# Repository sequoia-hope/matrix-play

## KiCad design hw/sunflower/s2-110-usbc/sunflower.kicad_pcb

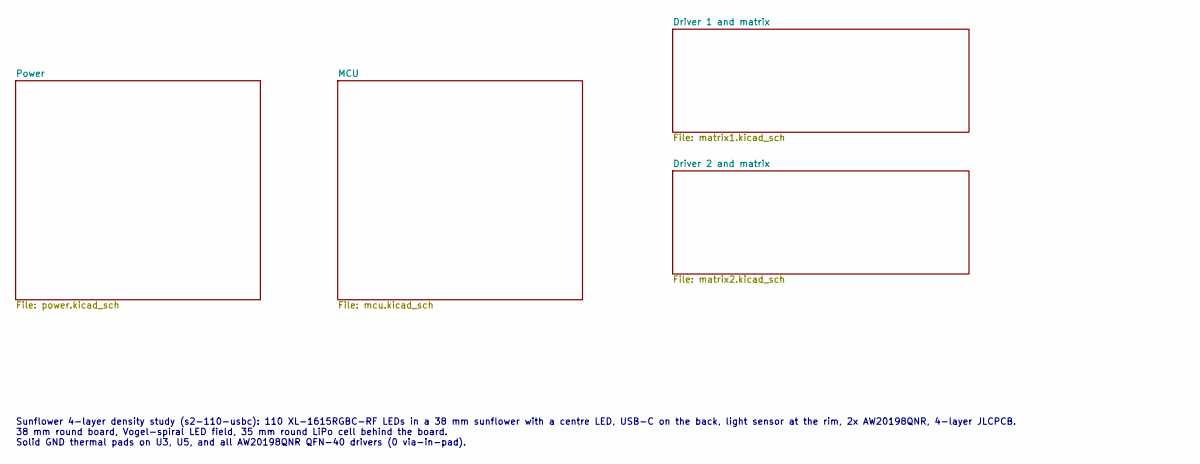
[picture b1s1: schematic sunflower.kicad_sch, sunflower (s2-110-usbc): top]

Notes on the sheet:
Sunflower 4-layer density study (s2-110-usbc): 110 XL-1615RGBC-RF LEDs in a 38 mm sunflower with a centre LED, USB-C on the back, light sensor at the rim, 2x AW20198QNR, 4-layer JLCPCB. 38 mm round board, Vogel-spiral LED field, 35 mm round LiPo cell behind the board. Solid GND thermal pads on U3, 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

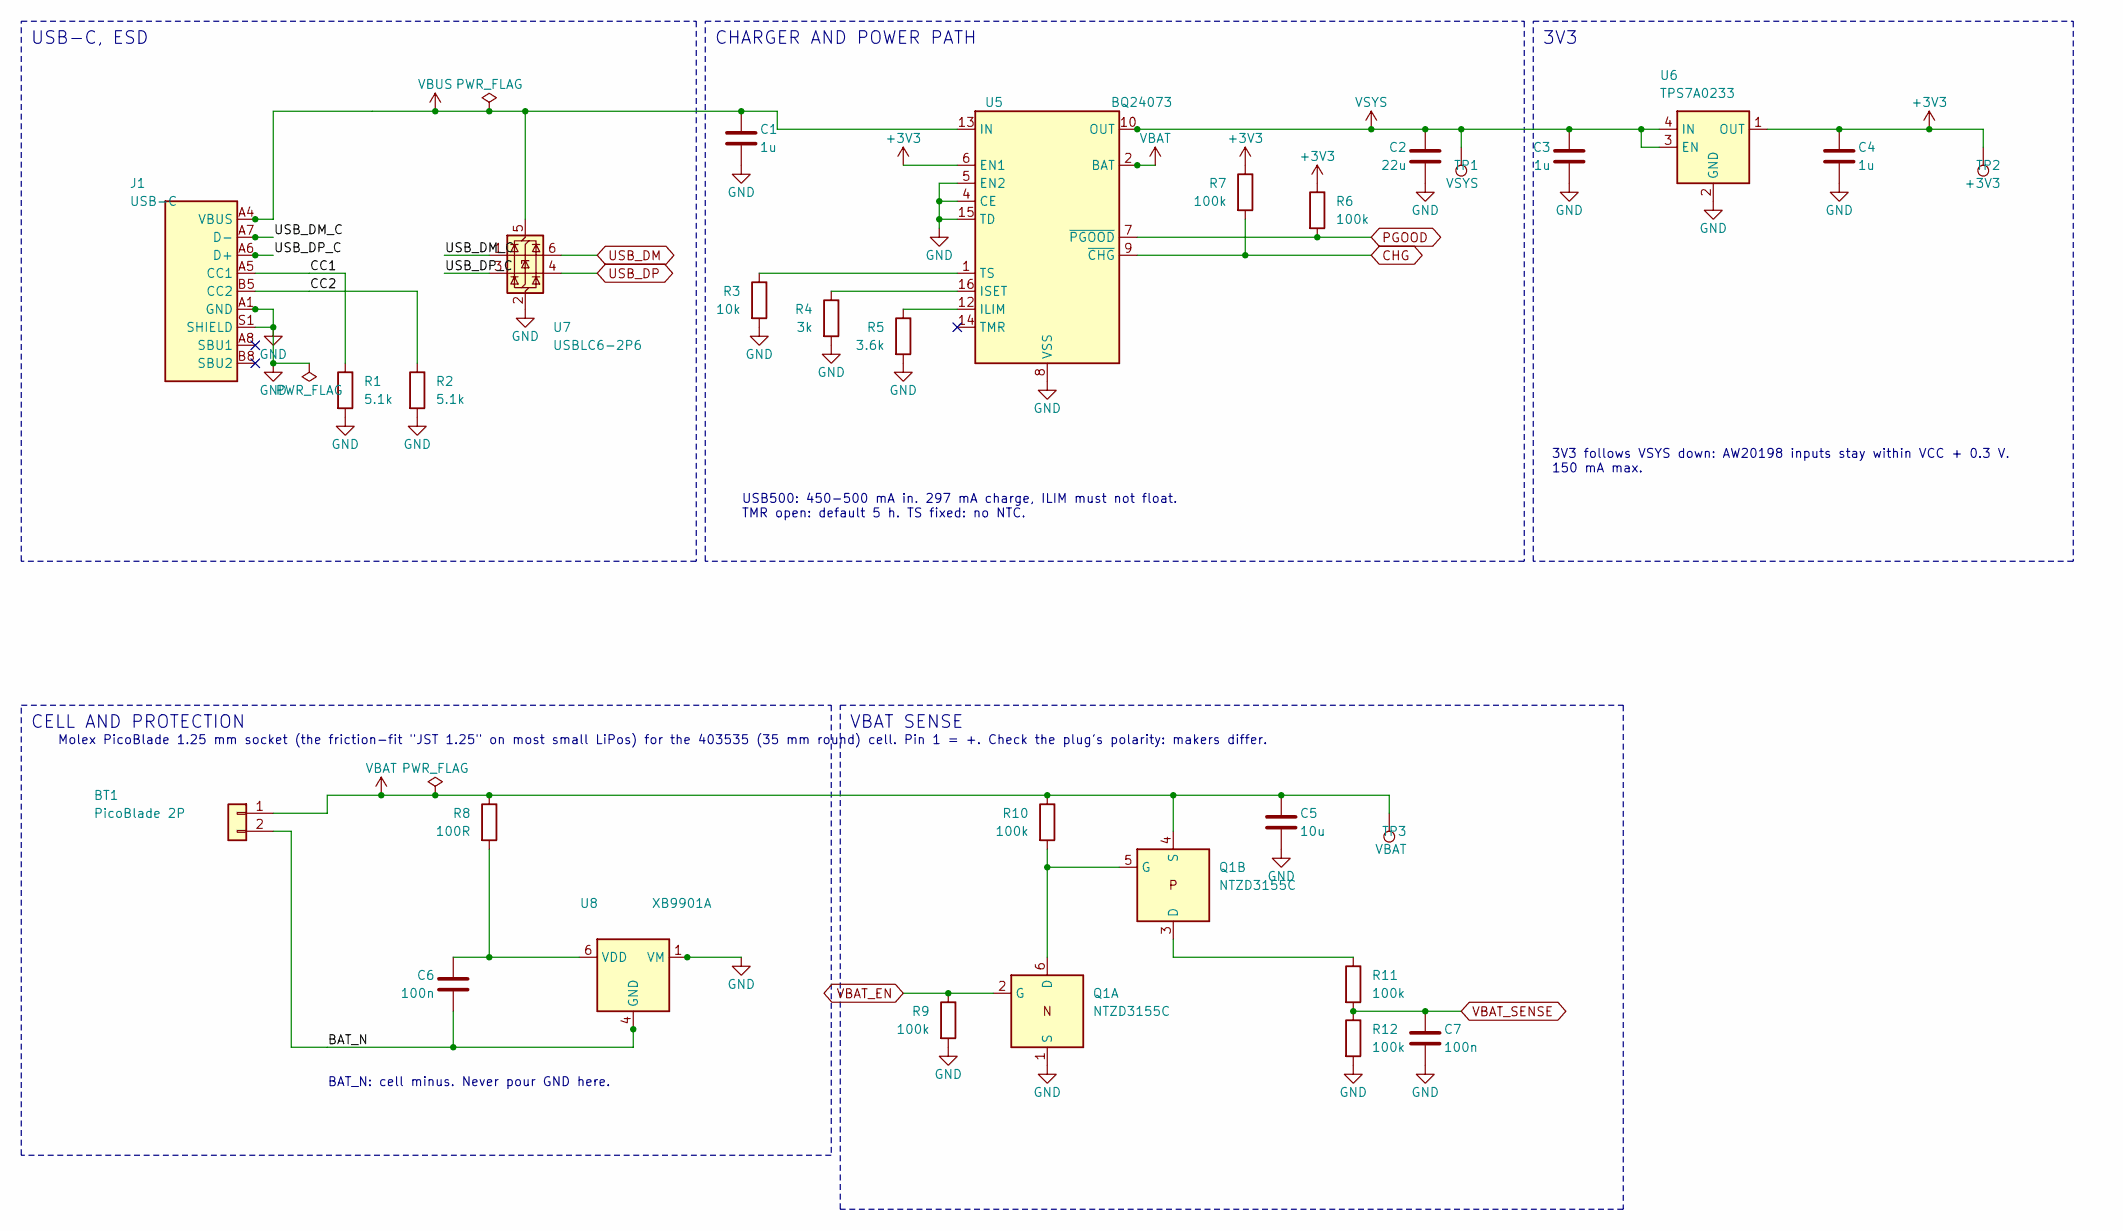
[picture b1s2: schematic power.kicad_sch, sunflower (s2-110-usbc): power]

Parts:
BT1: PicoBlade 2P; Molex_PicoBlade_53261-0271_1x02-1MP_P1.25mm_Horizontal; MPN 53261-0271; LCSC C177225
C1, C3, C4: 1u; C_0402_1005Metric; MPN CL05A105KA5NQNC; LCSC C52923
C2: 22u; C_0603_1608Metric; MPN CL10A226MP8NUNE; LCSC C86295
C5: 10u; C_0603_1608Metric; MPN CL10A106KP8NNNC; LCSC C19702
C6, C7: 100n; C_0402_1005Metric; MPN CL05B104KO5NNNC; LCSC C1525
J1: USB-C; USB_C_Receptacle_HRO_TYPE-C-31-M-12; MPN TYPE-C-31-M-12; LCSC C165948
Q1: NTZD3155C; SOT-563; MPN NTZD3155CT1G; LCSC C236117
R1, R2: 5.1k; R_0402_1005Metric; MPN 0402WGF5101TCE; LCSC C25905
R3: 10k; R_0402_1005Metric; MPN 0402WGF1002TCE; LCSC C25744
R4: 3k; R_0402_1005Metric; MPN 0402WGF3001TCE; LCSC C25784
R5: 3.6k; R_0402_1005Metric; MPN 0402WGF3601TCE; LCSC C25891
R6, R7, R9, R10, R11, R12: 100k; R_0402_1005Metric; MPN 0402WGF1003TCE; LCSC C25741
R8: 100R; R_0402_1005Metric; MPN 0402WGF1000TCE; LCSC C25076
TP1: VSYS; TestPoint_Pad_D1.0mm_CrtYd0.75
TP2: +3V3; TestPoint_Pad_D1.0mm_CrtYd0.75
TP3: VBAT; TestPoint_Pad_D1.0mm_CrtYd0.75
U5: BQ24073; QFN-16-1EP_3x3mm_P0.5mm_EP1.7x1.7mm; MPN BQ24073RGTR; LCSC C15220
U6: TPS7A0233; Texas_X2SON-4_1x1mm_P0.65mm; MPN TPS7A0233PDQNR; LCSC C2860046
U7: USBLC6-2P6; SOT-666; MPN USBLC6-2P6; LCSC C15999
U8: XB9901A; XySemi_DFN-6_1.8x1.4mm; MPN XB9901A; LCSC C669687

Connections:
+3V3: C4.1, R6.1, R7.1, TP2.1, U5.6 (EN1), U6.1 (OUT); also elsewhere on the board
/Power/BAT_N: BT1.2, C6.2, U8.4 (GND), U8.5 (GND)
/Power/CC1: J1.A5 (CC1), R1.1
/Power/CC2: J1.B5 (CC2), R2.1
/Power/USB_DM_C: J1.A7 (D-), J1.B7 (D-), U7.1 (I/O1)
/Power/USB_DP_C: J1.A6 (D+), J1.B6 (D+), U7.3 (I/O2)
CHG: R7.2, U5.9 (~CHG); also elsewhere on the board
unnamed: Q1.5 (G), Q1.6 (D), R10.2
unnamed: Q1.3 (D), R11.1
unnamed: R5.1, U5.12 (ILIM)
unnamed: R4.1, U5.16 (ISET)
unnamed: R3.1, U5.1 (TS)
unnamed: C6.1, R8.2, U8.6 (VDD)
PGOOD: R6.2, U5.7 (~PGOOD); also elsewhere on the board
USB_DM: U7.6 (I/O1); also elsewhere on the board
USB_DP: U7.4 (I/O2); also elsewhere on the board
VBAT_EN: Q1.2 (G), R9.1; also elsewhere on the board
VBAT_SENSE: C7.1, R11.2, R12.1; also elsewhere on the board
VSYS: C2.1, C3.1, TP1.1, U5.10 (OUT), U5.11 (OUT), U6.3 (EN), U6.4 (IN); also elsewhere on the board

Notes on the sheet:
USB-C, ESD
USB500: 450-500 mA in. 297 mA charge, ILIM must not float. TMR open: default 5 h. TS fixed: no NTC.
CHARGER AND POWER PATH
3V3 follows VSYS down: AW20198 inputs stay within VCC + 0.3 V. 150 mA max.
3V3
Molex PicoBlade 1.25 mm socket (the friction-fit "JST 1.25" on most small LiPos) for the 403535 (35 mm round) cell. Pin 1 = +. Check the plug's polarity: makers differ.
BAT_N: cell minus. Never pour GND here.
CELL AND PROTECTION
VBAT SENSE

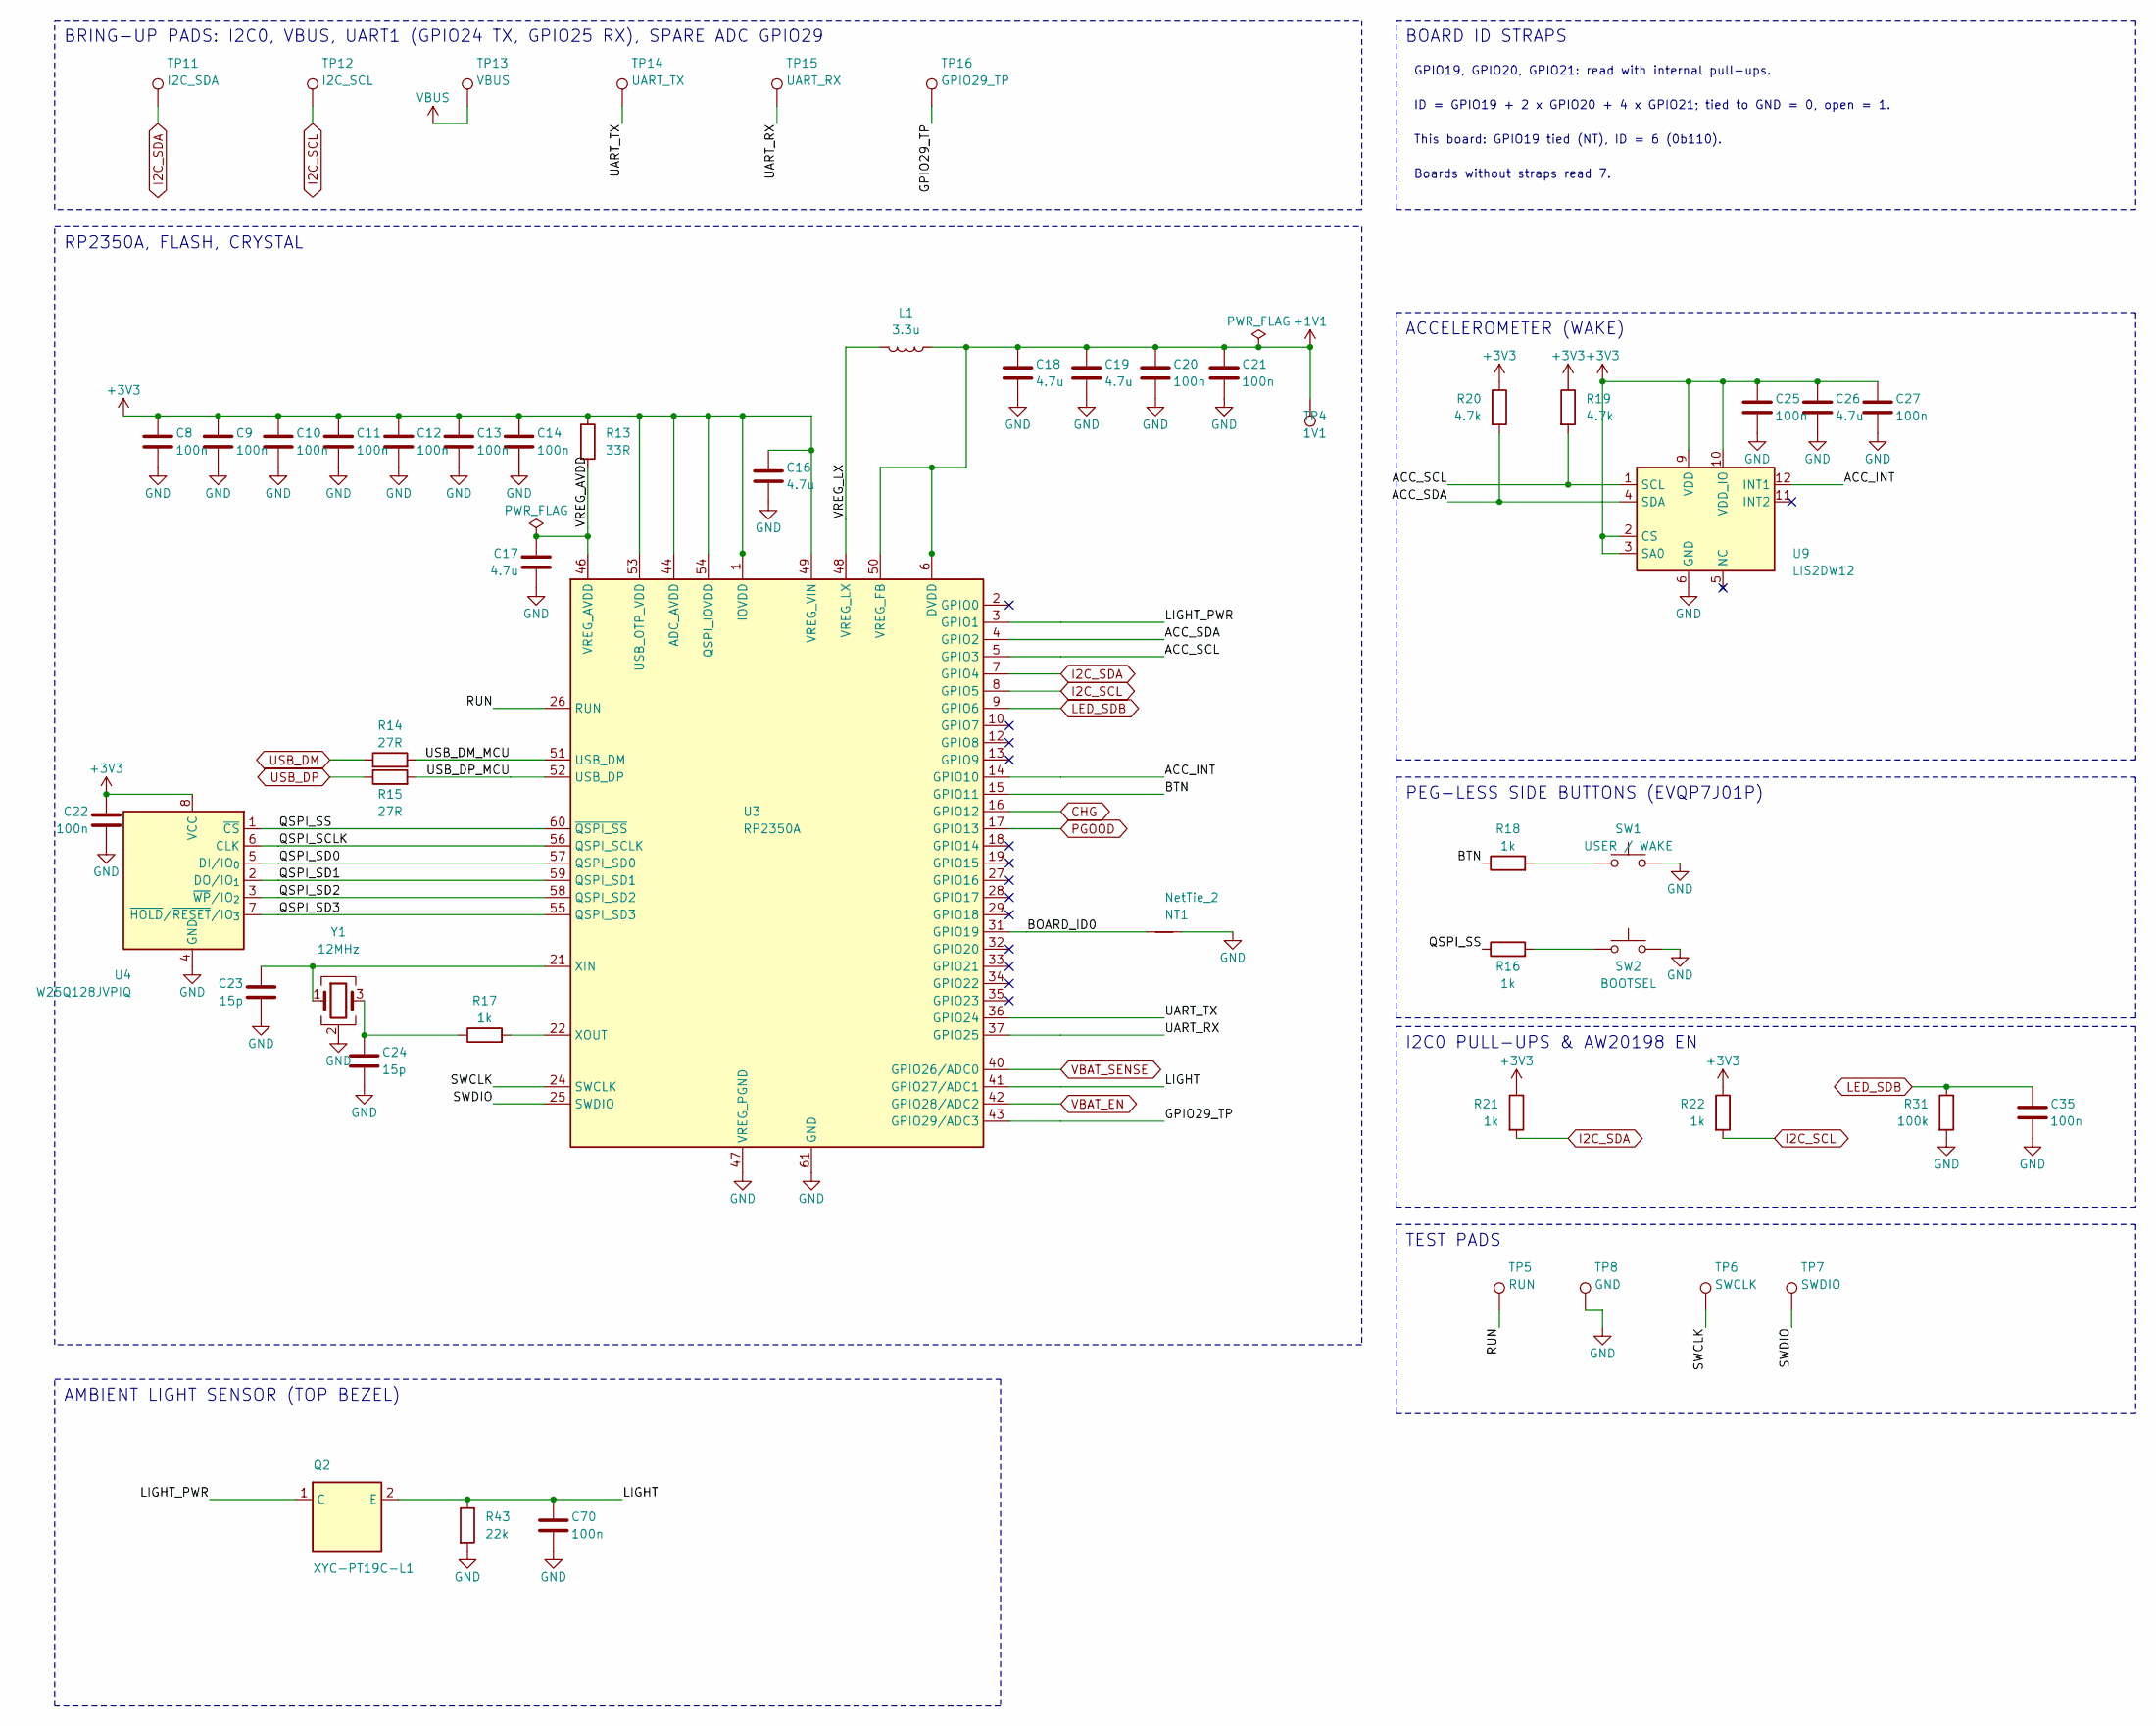
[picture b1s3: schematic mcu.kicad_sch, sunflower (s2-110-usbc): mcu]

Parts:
C8, C9, C10, C11, C12, C13, C14, C20, C21, C22, C25, C27, C35, C70: 100n; C_0402_1005Metric; MPN CL05B104KO5NNNC; LCSC C1525
C16, C18: 4.7u; C_0402_1005Metric_small_pads; MPN CL05A475MP5NRNC; LCSC C23733
C17, C19, C26: 4.7u; C_0402_1005Metric; MPN CL05A475MP5NRNC; LCSC C23733
C23, C24: 15p; C_0402_1005Metric; MPN 0402CG150J500NT; LCSC C1548
L1: 3.3u; L_pol_2016; MPN AOTA-B201610S3R3-101-T; LCSC C42411119
NT1: NetTie_2; NetTie-2_SMD_Pad0.5mm
Q2: XYC-PT19C-L1; SENSOR_ALS-PT19; MPN XYC-PT19C-L1; LCSC C2693594
R13: 33R; R_0402_1005Metric; MPN 0402WGF330JTCE; LCSC C25105
R14, R15: 27R; R_0402_1005Metric; MPN 0402WGF270JTCE; LCSC C25100
R16, R17, R18, R21, R22: 1k; R_0402_1005Metric; MPN 0402WGF1001TCE; LCSC C11702
R19, R20: 4.7k; R_0402_1005Metric; MPN 0402WGF4701TCE; LCSC C25900
R31: 100k; R_0402_1005Metric; MPN 0402WGF1003TCE; LCSC C25741
R43: 22k; R_0402_1005Metric; MPN 0402WGF2202TCE; LCSC C25768
SW1: USER / WAKE; SW_Panasonic_EVQP7J; MPN EVQP7J01P; LCSC C2828254
SW2: BOOTSEL; SW_Panasonic_EVQP7J; MPN EVQP7J01P; LCSC C2828254
TP4: 1V1; TestPoint_Pad_D1.0mm_CrtYd0.75
TP5: RUN; TestPoint_Pad_D1.0mm_CrtYd0.75
TP6: SWCLK; TestPoint_Pad_D1.0mm_CrtYd0.75
TP7: SWDIO; TestPoint_Pad_D1.0mm_CrtYd0.75
TP8: GND; TestPoint_Pad_D1.0mm_CrtYd0.75
TP11: I2C_SDA; TestPoint_Pad_D1.0mm_CrtYd0.75
TP12: I2C_SCL; TestPoint_Pad_D1.0mm_CrtYd0.75
TP13: VBUS; TestPoint_Pad_D1.0mm_CrtYd0.75
TP14: UART_TX; TestPoint_Pad_D1.0mm_CrtYd0.75
TP15: UART_RX; TestPoint_Pad_D1.0mm_CrtYd0.75
TP16: GPIO29_TP; TestPoint_Pad_D1.0mm_CrtYd0.75
U3: RP2350A; RP2350-QFN-60-1EP_7x7_P0.4mm_EP3.4x3.4mm_ThermalVias; MPN RP2350A; LCSC C42411118
U4: W25Q128JVPIQ; WSON-8_6x5mm_P1.27mm_NoEPCopper; MPN W25Q128JVPIQ; LCSC C190862
U9: LIS2DW12; LGA-12_2x2mm_P0.5mm; MPN LIS2DW12TR; LCSC C189624
Y1: 12MHz; Crystal_SMD_3225-4Pin_3.2x2.5mm; MPN ABM8-272-T3; LCSC C20625731

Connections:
+3V3: C8.1, C9.1, C10.1, C11.1, C12.1, C13.1, C14.1, C16.1, C22.1, C25.1, C26.1, C27.1, R13.1, R19.1, R20.1, R21.1, R22.1, U3.1 (IOVDD), U3.11 (IOVDD), U3.20 (IOVDD), U3.30 (IOVDD), U3.38 (IOVDD), U3.44 (ADC_AVDD), U3.45 (IOVDD), U3.49 (VREG_VIN), U3.53 (USB_OTP_VDD), U3.54 (QSPI_IOVDD), U4.8 (VCC), U9.2 (CS), U9.3 (SA0), U9.9 (VDD), U9.10 (VDD_IO); also elsewhere on the board
/MCU/ACC_INT: U3.14 (GPIO10), U9.12 (INT1)
/MCU/ACC_SCL: R19.2, U3.5 (GPIO3), U9.1 (SCL)
/MCU/ACC_SDA: R20.2, U3.4 (GPIO2), U9.4 (SDA)
/MCU/BOARD_ID0: NT1.1, U3.31 (GPIO19)
/MCU/BTN: R18.1, U3.15 (GPIO11)
/MCU/GPIO29_TP: TP16.1, U3.43 (GPIO29/ADC3)
/MCU/LIGHT: C70.1, Q2.2 (E), R43.1, U3.41 (GPIO27/ADC1)
/MCU/LIGHT_PWR: Q2.1 (C), U3.3 (GPIO1)
/MCU/QSPI_SCLK: U3.56 (QSPI_SCLK), U4.6 (CLK)
/MCU/QSPI_SD0: U3.57 (QSPI_SD0), U4.5 (DI/IO_{0})
/MCU/QSPI_SD1: U3.59 (QSPI_SD1), U4.2 (DO/IO_{1})
/MCU/QSPI_SD2: U3.58 (QSPI_SD2), U4.3 (~WP/IO_{2})
/MCU/QSPI_SD3: U3.55 (QSPI_SD3), U4.7 (~HOLD/~RESET/IO_{3})
/MCU/QSPI_SS: R16.1, U3.60 (~QSPI_SS), U4.1 (~CS)
/MCU/RUN: TP5.1, U3.26 (RUN)
/MCU/SWCLK: TP6.1, U3.24 (SWCLK)
/MCU/SWDIO: TP7.1, U3.25 (SWDIO)
/MCU/UART_RX: TP15.1, U3.37 (GPIO25)
/MCU/UART_TX: TP14.1, U3.36 (GPIO24)
/MCU/USB_DM_MCU: R14.2, U3.51 (USB_DM)
/MCU/USB_DP_MCU: R15.2, U3.52 (USB_DP)
/MCU/VREG_LX: L1.2, U3.48 (VREG_LX)
CHG: U3.16 (GPIO12); also elsewhere on the board
I2C_SCL: R22.2, TP12.1, U3.8 (GPIO5); also elsewhere on the board
I2C_SDA: R21.2, TP11.1, U3.7 (GPIO4); also elsewhere on the board
LED_SDB: C35.1, R31.1, U3.9 (GPIO6); also elsewhere on the board
unnamed: C24.1, R17.1, Y1.3
unnamed: R16.2, SW2.1
unnamed: R18.2, SW1.1
unnamed: C23.1, U3.21 (XIN), Y1.1
unnamed: R17.2, U3.22 (XOUT)
PGOOD: U3.17 (GPIO13); also elsewhere on the board
USB_DM: R14.1; also elsewhere on the board
USB_DP: R15.1; also elsewhere on the board
VBAT_EN: U3.42 (GPIO28/ADC2); also elsewhere on the board
VBAT_SENSE: U3.40 (GPIO26/ADC0); also elsewhere on the board

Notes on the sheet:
RP2350A, FLASH, CRYSTAL
ACCELEROMETER (WAKE)
PEG-LESS SIDE BUTTONS (EVQP7J01P)
I2C0 PULL-UPS & AW20198 EN
TEST PADS
BRING-UP PADS: I2C0, VBUS, UART1 (GPIO24 TX, GPIO25 RX), SPARE ADC GPIO29
GPIO19, GPIO20, GPIO21: read with internal pull-ups.
ID = GPIO19 + 2 x GPIO20 + 4 x GPIO21; tied to GND = 0, open = 1.
This board: GPIO19 tied (NT), ID = 6 (0b110).
Boards without straps read 7.
BOARD ID STRAPS
AMBIENT LIGHT SENSOR (TOP BEZEL)

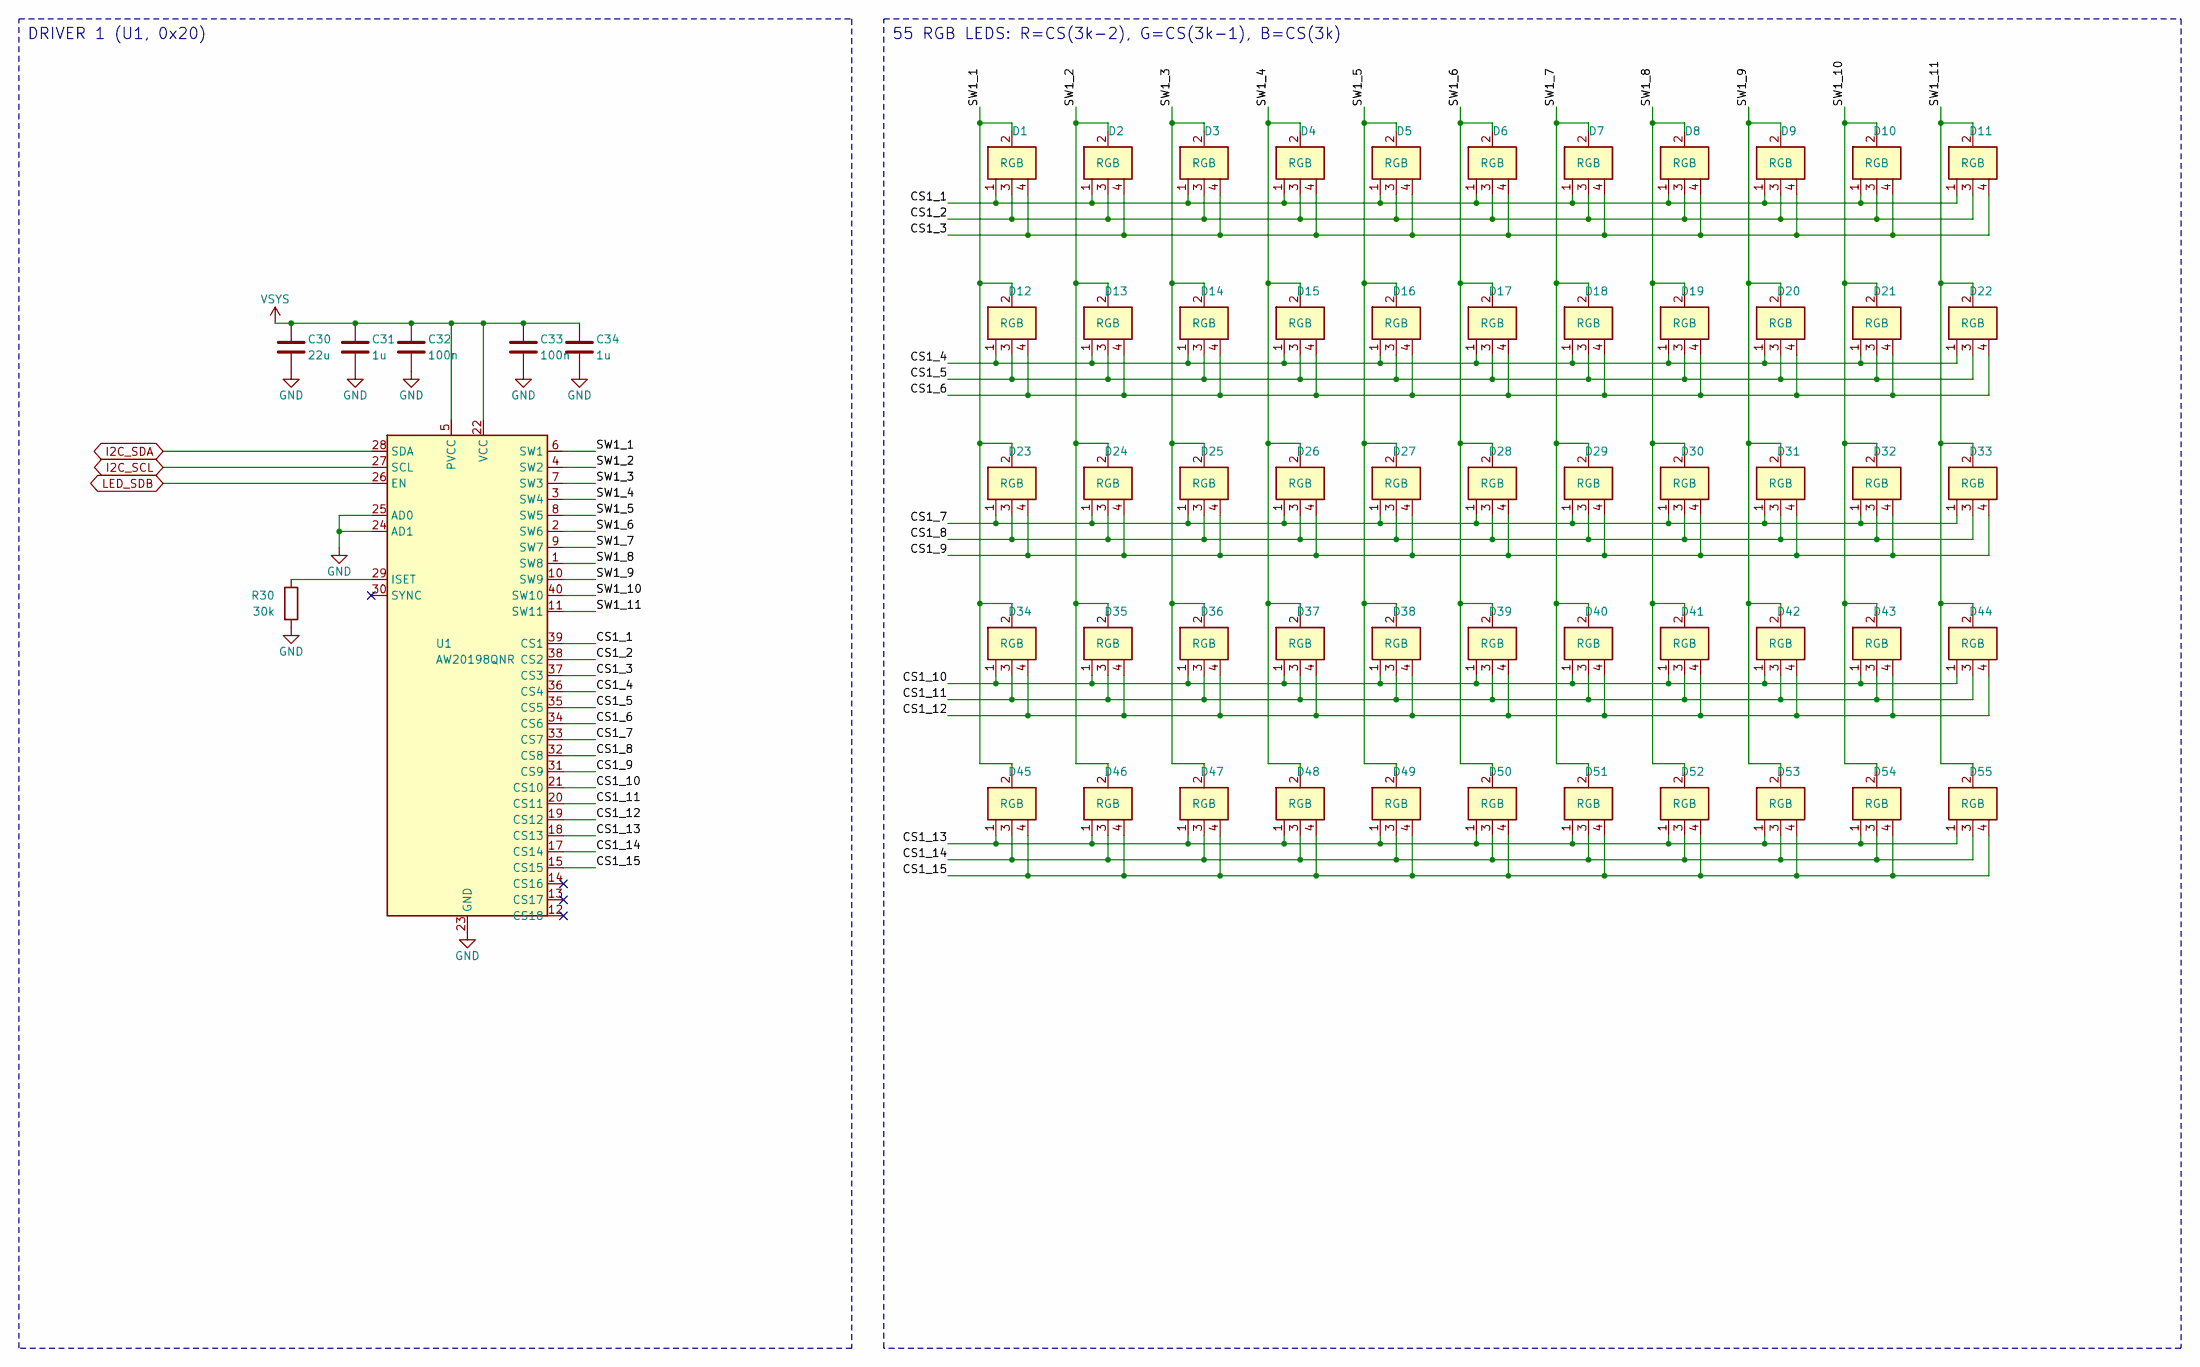
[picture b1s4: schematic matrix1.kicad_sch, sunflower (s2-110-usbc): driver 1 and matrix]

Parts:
C30: 22u; C_0603_1608Metric; MPN CL10A226MP8NUNE; LCSC C86295
C31, C34: 1u; C_0402_1005Metric; MPN CL05A105KA5NQNC; LCSC C52923
C32, C33: 100n; C_0402_1005Metric; MPN CL05B104KO5NNNC; LCSC C1525
D1, D2, D3, D4, D5, D6, D7, D8, D9, D10, D11, D12, D13, D14, D15, D16, D17, D18, D19, D20, D21, D22, D23, D24, D25, D26, D27, D28, D29, D30, D31, D32, D33, D34, D35, D36, D37, D38, D39, D40, D41, D42, D43, D44, D45, D46, D47, D48, D49, D50, D51, D52, D53, D54, D55: RGB; LED_XL-1615RGBC; MPN XL-1615RGBC-RF; LCSC C965840
R30: 30k; R_0402_1005Metric; MPN 0402WGF3002TCE; LCSC C25776
U1: AW20198QNR; AW20198_QFN-40-1EP_5x5mm_P0.4mm_EP3.4x3.4mm; MPN AW20198QNR; LCSC C5137654

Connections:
/Driver 1 and matrix/CS1_1: D1.1 (R), D2.1 (R), D3.1 (R), D4.1 (R), D5.1 (R), D6.1 (R), D7.1 (R), D8.1 (R), D9.1 (R), D10.1 (R), D11.1 (R), U1.39 (CS1)
/Driver 1 and matrix/CS1_2: D1.3 (G), D2.3 (G), D3.3 (G), D4.3 (G), D5.3 (G), D6.3 (G), D7.3 (G), D8.3 (G), D9.3 (G), D10.3 (G), D11.3 (G), U1.38 (CS2)
/Driver 1 and matrix/CS1_3: D1.4 (B), D2.4 (B), D3.4 (B), D4.4 (B), D5.4 (B), D6.4 (B), D7.4 (B), D8.4 (B), D9.4 (B), D10.4 (B), D11.4 (B), U1.37 (CS3)
/Driver 1 and matrix/CS1_4: D12.1 (R), D13.1 (R), D14.1 (R), D15.1 (R), D16.1 (R), D17.1 (R), D18.1 (R), D19.1 (R), D20.1 (R), D21.1 (R), D22.1 (R), U1.36 (CS4)
/Driver 1 and matrix/CS1_5: D12.3 (G), D13.3 (G), D14.3 (G), D15.3 (G), D16.3 (G), D17.3 (G), D18.3 (G), D19.3 (G), D20.3 (G), D21.3 (G), D22.3 (G), U1.35 (CS5)
/Driver 1 and matrix/CS1_6: D12.4 (B), D13.4 (B), D14.4 (B), D15.4 (B), D16.4 (B), D17.4 (B), D18.4 (B), D19.4 (B), D20.4 (B), D21.4 (B), D22.4 (B), U1.34 (CS6)
/Driver 1 and matrix/CS1_7: D23.1 (R), D24.1 (R), D25.1 (R), D26.1 (R), D27.1 (R), D28.1 (R), D29.1 (R), D30.1 (R), D31.1 (R), D32.1 (R), D33.1 (R), U1.33 (CS7)
/Driver 1 and matrix/CS1_8: D23.3 (G), D24.3 (G), D25.3 (G), D26.3 (G), D27.3 (G), D28.3 (G), D29.3 (G), D30.3 (G), D31.3 (G), D32.3 (G), D33.3 (G), U1.32 (CS8)
/Driver 1 and matrix/CS1_9: D23.4 (B), D24.4 (B), D25.4 (B), D26.4 (B), D27.4 (B), D28.4 (B), D29.4 (B), D30.4 (B), D31.4 (B), D32.4 (B), D33.4 (B), U1.31 (CS9)
/Driver 1 and matrix/CS1_10: D34.1 (R), D35.1 (R), D36.1 (R), D37.1 (R), D38.1 (R), D39.1 (R), D40.1 (R), D41.1 (R), D42.1 (R), D43.1 (R), D44.1 (R), U1.21 (CS10)
/Driver 1 and matrix/CS1_11: D34.3 (G), D35.3 (G), D36.3 (G), D37.3 (G), D38.3 (G), D39.3 (G), D40.3 (G), D41.3 (G), D42.3 (G), D43.3 (G), D44.3 (G), U1.20 (CS11)
/Driver 1 and matrix/CS1_12: D34.4 (B), D35.4 (B), D36.4 (B), D37.4 (B), D38.4 (B), D39.4 (B), D40.4 (B), D41.4 (B), D42.4 (B), D43.4 (B), D44.4 (B), U1.19 (CS12)
/Driver 1 and matrix/CS1_13: D45.1 (R), D46.1 (R), D47.1 (R), D48.1 (R), D49.1 (R), D50.1 (R), D51.1 (R), D52.1 (R), D53.1 (R), D54.1 (R), D55.1 (R), U1.18 (CS13)
/Driver 1 and matrix/CS1_14: D45.3 (G), D46.3 (G), D47.3 (G), D48.3 (G), D49.3 (G), D50.3 (G), D51.3 (G), D52.3 (G), D53.3 (G), D54.3 (G), D55.3 (G), U1.17 (CS14)
/Driver 1 and matrix/CS1_15: D45.4 (B), D46.4 (B), D47.4 (B), D48.4 (B), D49.4 (B), D50.4 (B), D51.4 (B), D52.4 (B), D53.4 (B), D54.4 (B), D55.4 (B), U1.15 (CS15)
/Driver 1 and matrix/SW1_1: D1.2 (A), D12.2 (A), D23.2 (A), D34.2 (A), D45.2 (A), U1.6 (SW1)
/Driver 1 and matrix/SW1_2: D2.2 (A), D13.2 (A), D24.2 (A), D35.2 (A), D46.2 (A), U1.4 (SW2)
/Driver 1 and matrix/SW1_3: D3.2 (A), D14.2 (A), D25.2 (A), D36.2 (A), D47.2 (A), U1.7 (SW3)
/Driver 1 and matrix/SW1_4: D4.2 (A), D15.2 (A), D26.2 (A), D37.2 (A), D48.2 (A), U1.3 (SW4)
/Driver 1 and matrix/SW1_5: D5.2 (A), D16.2 (A), D27.2 (A), D38.2 (A), D49.2 (A), U1.8 (SW5)
/Driver 1 and matrix/SW1_6: D6.2 (A), D17.2 (A), D28.2 (A), D39.2 (A), D50.2 (A), U1.2 (SW6)
/Driver 1 and matrix/SW1_7: D7.2 (A), D18.2 (A), D29.2 (A), D40.2 (A), D51.2 (A), U1.9 (SW7)
/Driver 1 and matrix/SW1_8: D8.2 (A), D19.2 (A), D30.2 (A), D41.2 (A), D52.2 (A), U1.1 (SW8)
/Driver 1 and matrix/SW1_9: D9.2 (A), D20.2 (A), D31.2 (A), D42.2 (A), D53.2 (A), U1.10 (SW9)
/Driver 1 and matrix/SW1_10: D10.2 (A), D21.2 (A), D32.2 (A), D43.2 (A), D54.2 (A), U1.40 (SW10)
/Driver 1 and matrix/SW1_11: D11.2 (A), D22.2 (A), D33.2 (A), D44.2 (A), D55.2 (A), U1.11 (SW11)
I2C_SCL: U1.27 (SCL); also elsewhere on the board
I2C_SDA: U1.28 (SDA); also elsewhere on the board
LED_SDB: U1.26 (EN); also elsewhere on the board
unnamed: R30.1, U1.29 (ISET)
VSYS: C30.1, C31.1, C32.1, C33.1, C34.1, U1.5 (PVCC), U1.22 (VCC); also elsewhere on the board

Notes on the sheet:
DRIVER 1 (U1, 0x20)
55 RGB LEDS: R=CS(3k-2), G=CS(3k-1), B=CS(3k)

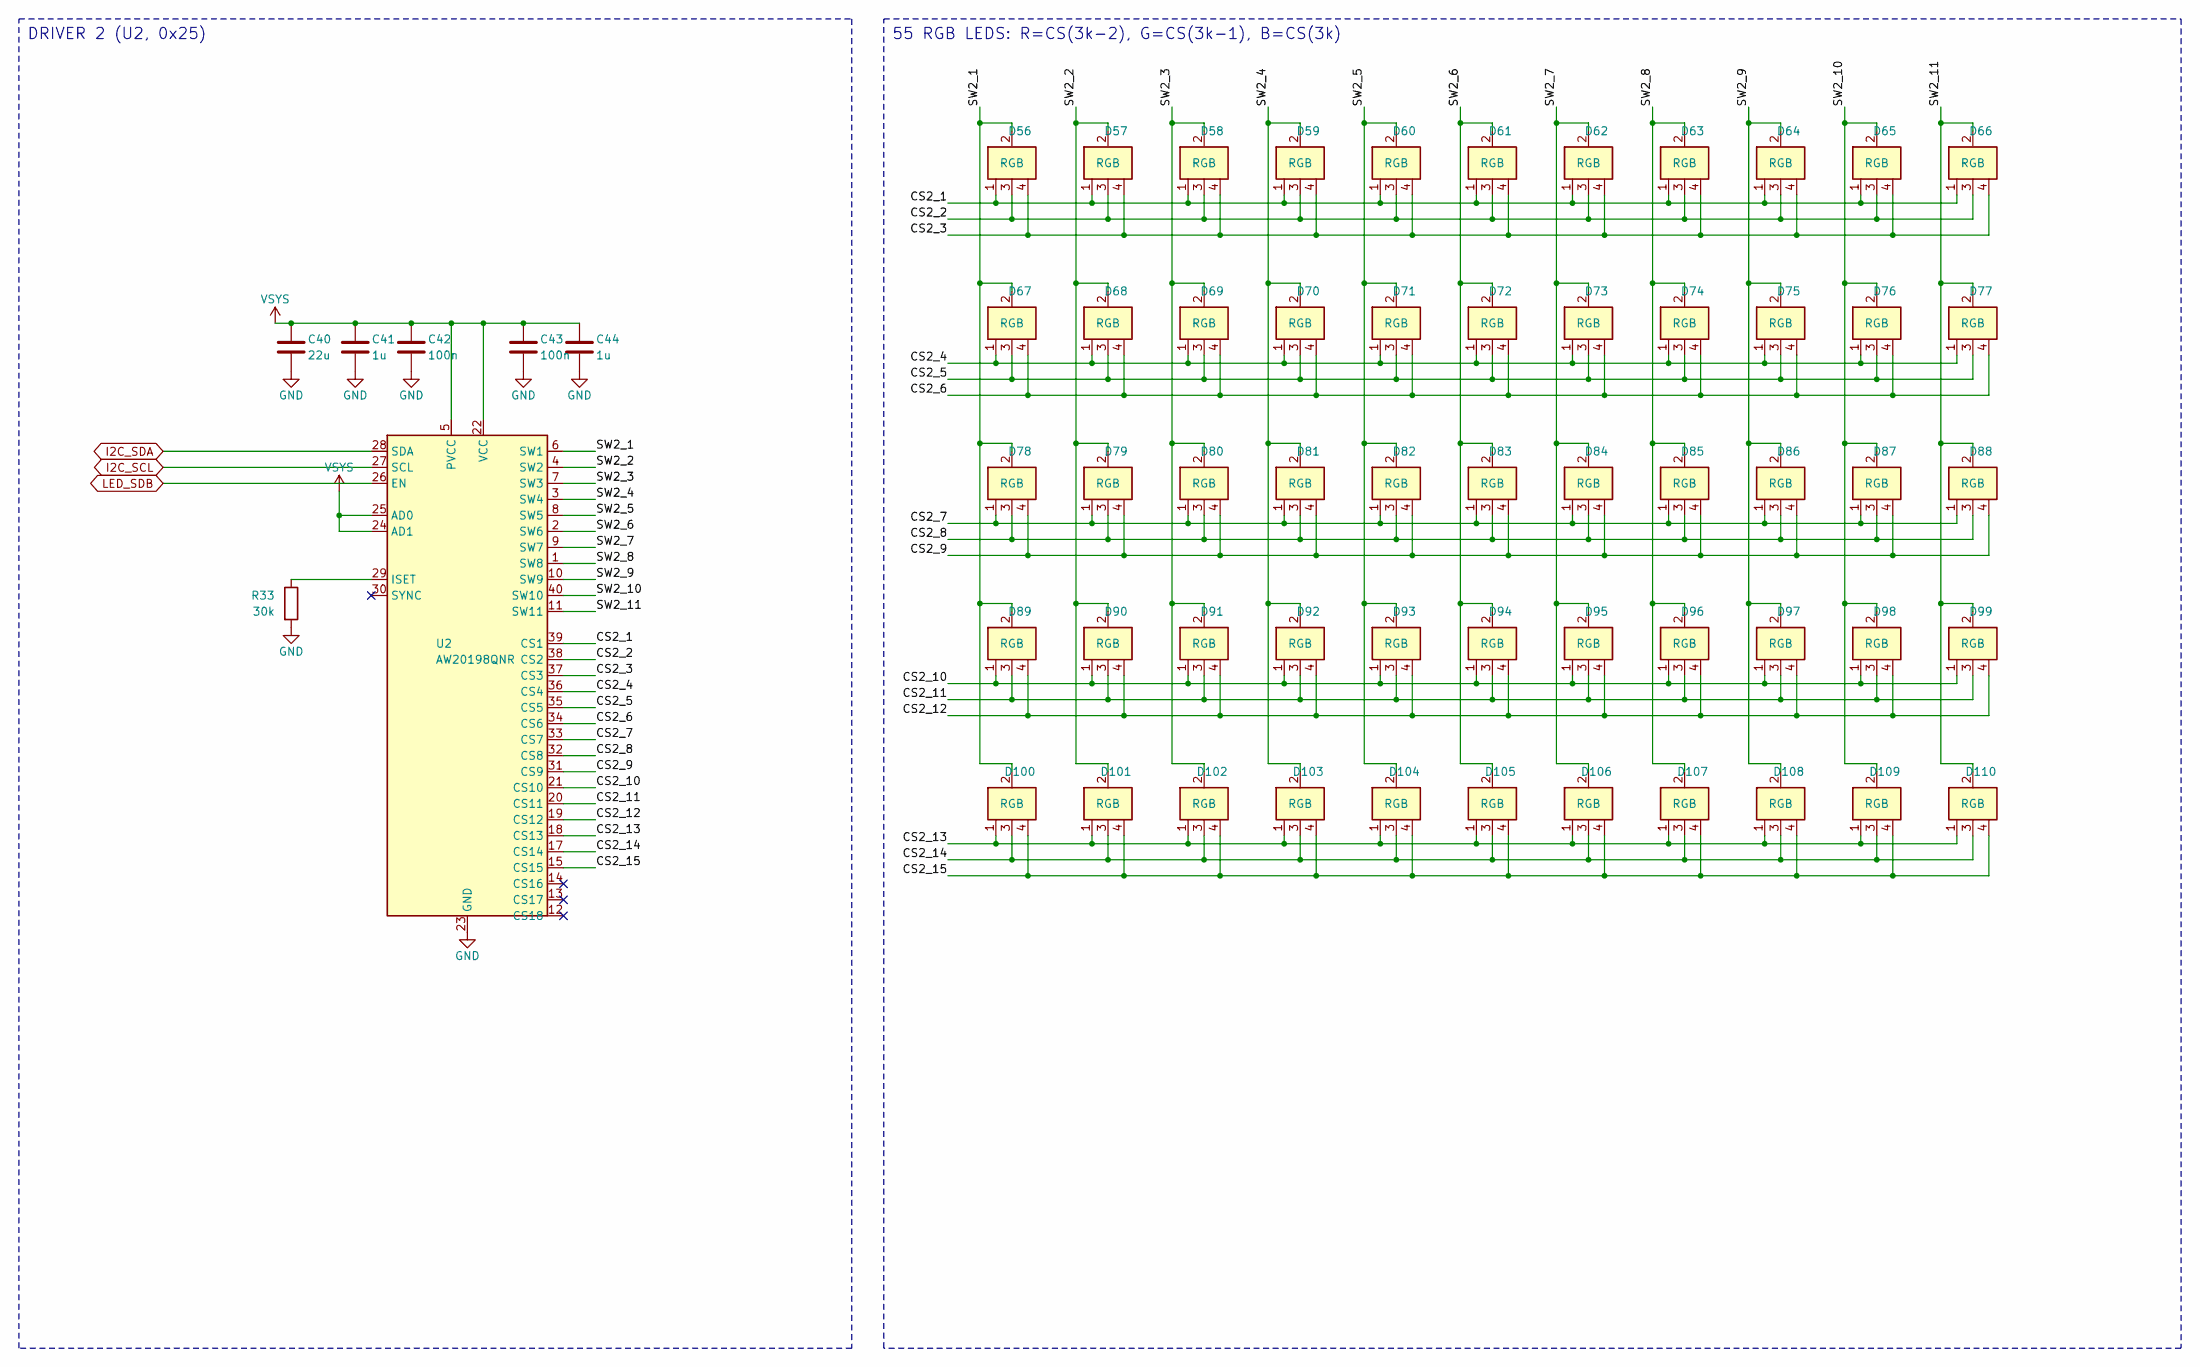
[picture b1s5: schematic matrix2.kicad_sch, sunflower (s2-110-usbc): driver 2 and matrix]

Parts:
C40: 22u; C_0603_1608Metric; MPN CL10A226MP8NUNE; LCSC C86295
C41, C44: 1u; C_0402_1005Metric; MPN CL05A105KA5NQNC; LCSC C52923
C42, C43: 100n; C_0402_1005Metric; MPN CL05B104KO5NNNC; LCSC C1525
D56, D57, D58, D59, D60, D61, D62, D63, D64, D65, D66, D67, D68, D69, D70, D71, D72, D73, D74, D75, D76, D77, D78, D79, D80, D81, D82, D83, D84, D85, D86, D87, D88, D89, D90, D91, D92, D93, D94, D95, D96, D97, D98, D99, D100, D101, D102, D103, D104, D105, D106, D107, D108, D109, D110: RGB; LED_XL-1615RGBC; MPN XL-1615RGBC-RF; LCSC C965840
R33: 30k; R_0402_1005Metric; MPN 0402WGF3002TCE; LCSC C25776
U2: AW20198QNR; AW20198_QFN-40-1EP_5x5mm_P0.4mm_EP3.4x3.4mm; MPN AW20198QNR; LCSC C5137654

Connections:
/Driver 2 and matrix/CS2_1: D56.1 (R), D57.1 (R), D58.1 (R), D59.1 (R), D60.1 (R), D61.1 (R), D62.1 (R), D63.1 (R), D64.1 (R), D65.1 (R), D66.1 (R), U2.39 (CS1)
/Driver 2 and matrix/CS2_2: D56.3 (G), D57.3 (G), D58.3 (G), D59.3 (G), D60.3 (G), D61.3 (G), D62.3 (G), D63.3 (G), D64.3 (G), D65.3 (G), D66.3 (G), U2.38 (CS2)
/Driver 2 and matrix/CS2_3: D56.4 (B), D57.4 (B), D58.4 (B), D59.4 (B), D60.4 (B), D61.4 (B), D62.4 (B), D63.4 (B), D64.4 (B), D65.4 (B), D66.4 (B), U2.37 (CS3)
/Driver 2 and matrix/CS2_4: D67.1 (R), D68.1 (R), D69.1 (R), D70.1 (R), D71.1 (R), D72.1 (R), D73.1 (R), D74.1 (R), D75.1 (R), D76.1 (R), D77.1 (R), U2.36 (CS4)
/Driver 2 and matrix/CS2_5: D67.3 (G), D68.3 (G), D69.3 (G), D70.3 (G), D71.3 (G), D72.3 (G), D73.3 (G), D74.3 (G), D75.3 (G), D76.3 (G), D77.3 (G), U2.35 (CS5)
/Driver 2 and matrix/CS2_6: D67.4 (B), D68.4 (B), D69.4 (B), D70.4 (B), D71.4 (B), D72.4 (B), D73.4 (B), D74.4 (B), D75.4 (B), D76.4 (B), D77.4 (B), U2.34 (CS6)
/Driver 2 and matrix/CS2_7: D78.1 (R), D79.1 (R), D80.1 (R), D81.1 (R), D82.1 (R), D83.1 (R), D84.1 (R), D85.1 (R), D86.1 (R), D87.1 (R), D88.1 (R), U2.33 (CS7)
/Driver 2 and matrix/CS2_8: D78.3 (G), D79.3 (G), D80.3 (G), D81.3 (G), D82.3 (G), D83.3 (G), D84.3 (G), D85.3 (G), D86.3 (G), D87.3 (G), D88.3 (G), U2.32 (CS8)
/Driver 2 and matrix/CS2_9: D78.4 (B), D79.4 (B), D80.4 (B), D81.4 (B), D82.4 (B), D83.4 (B), D84.4 (B), D85.4 (B), D86.4 (B), D87.4 (B), D88.4 (B), U2.31 (CS9)
/Driver 2 and matrix/CS2_10: D89.1 (R), D90.1 (R), D91.1 (R), D92.1 (R), D93.1 (R), D94.1 (R), D95.1 (R), D96.1 (R), D97.1 (R), D98.1 (R), D99.1 (R), U2.21 (CS10)
/Driver 2 and matrix/CS2_11: D89.3 (G), D90.3 (G), D91.3 (G), D92.3 (G), D93.3 (G), D94.3 (G), D95.3 (G), D96.3 (G), D97.3 (G), D98.3 (G), D99.3 (G), U2.20 (CS11)
/Driver 2 and matrix/CS2_12: D89.4 (B), D90.4 (B), D91.4 (B), D92.4 (B), D93.4 (B), D94.4 (B), D95.4 (B), D96.4 (B), D97.4 (B), D98.4 (B), D99.4 (B), U2.19 (CS12)
/Driver 2 and matrix/CS2_13: D100.1 (R), D101.1 (R), D102.1 (R), D103.1 (R), D104.1 (R), D105.1 (R), D106.1 (R), D107.1 (R), D108.1 (R), D109.1 (R), D110.1 (R), U2.18 (CS13)
/Driver 2 and matrix/CS2_14: D100.3 (G), D101.3 (G), D102.3 (G), D103.3 (G), D104.3 (G), D105.3 (G), D106.3 (G), D107.3 (G), D108.3 (G), D109.3 (G), D110.3 (G), U2.17 (CS14)
/Driver 2 and matrix/CS2_15: D100.4 (B), D101.4 (B), D102.4 (B), D103.4 (B), D104.4 (B), D105.4 (B), D106.4 (B), D107.4 (B), D108.4 (B), D109.4 (B), D110.4 (B), U2.15 (CS15)
/Driver 2 and matrix/SW2_1: D56.2 (A), D67.2 (A), D78.2 (A), D89.2 (A), D100.2 (A), U2.6 (SW1)
/Driver 2 and matrix/SW2_2: D57.2 (A), D68.2 (A), D79.2 (A), D90.2 (A), D101.2 (A), U2.4 (SW2)
/Driver 2 and matrix/SW2_3: D58.2 (A), D69.2 (A), D80.2 (A), D91.2 (A), D102.2 (A), U2.7 (SW3)
/Driver 2 and matrix/SW2_4: D59.2 (A), D70.2 (A), D81.2 (A), D92.2 (A), D103.2 (A), U2.3 (SW4)
/Driver 2 and matrix/SW2_5: D60.2 (A), D71.2 (A), D82.2 (A), D93.2 (A), D104.2 (A), U2.8 (SW5)
/Driver 2 and matrix/SW2_6: D61.2 (A), D72.2 (A), D83.2 (A), D94.2 (A), D105.2 (A), U2.2 (SW6)
/Driver 2 and matrix/SW2_7: D62.2 (A), D73.2 (A), D84.2 (A), D95.2 (A), D106.2 (A), U2.9 (SW7)
/Driver 2 and matrix/SW2_8: D63.2 (A), D74.2 (A), D85.2 (A), D96.2 (A), D107.2 (A), U2.1 (SW8)
/Driver 2 and matrix/SW2_9: D64.2 (A), D75.2 (A), D86.2 (A), D97.2 (A), D108.2 (A), U2.10 (SW9)
/Driver 2 and matrix/SW2_10: D65.2 (A), D76.2 (A), D87.2 (A), D98.2 (A), D109.2 (A), U2.40 (SW10)
/Driver 2 and matrix/SW2_11: D66.2 (A), D77.2 (A), D88.2 (A), D99.2 (A), D110.2 (A), U2.11 (SW11)
I2C_SCL: U2.27 (SCL); also elsewhere on the board
I2C_SDA: U2.28 (SDA); also elsewhere on the board
LED_SDB: U2.26 (EN); also elsewhere on the board
unnamed: R33.1, U2.29 (ISET)
VSYS: C40.1, C41.1, C42.1, C43.1, C44.1, U2.5 (PVCC), U2.22 (VCC), U2.24 (AD1), U2.25 (AD0); also elsewhere on the board

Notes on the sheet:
DRIVER 2 (U2, 0x25)
55 RGB LEDS: R=CS(3k-2), G=CS(3k-1), B=CS(3k)

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

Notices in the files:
hw/sunflower/pn-dense-1d/matrix1.kicad_sch:
CERN-OHL-P-2.0
